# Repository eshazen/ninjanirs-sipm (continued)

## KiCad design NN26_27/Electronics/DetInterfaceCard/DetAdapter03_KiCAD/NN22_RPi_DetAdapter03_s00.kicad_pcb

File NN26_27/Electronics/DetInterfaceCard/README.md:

## Detector card V03

Two variants:

| Designator | NN24-26        | NN27  | Notes                             |
|------------|----------------|-------|-----------------------------------|
| R71        | DNP            | 0 Ohm | New component / designator        |
| LF1        | BLM18AG601SN1D | DNP   | Ferrite 600 Ohm @ 100 MHz, 500 mA |

Additional components could be DNP’d in NN27 if desired, such as U13 and C104.

**2026-08-24**

Trying to order.  Two problem parts:

C89 etc.  10uF X5R 0402

D1-D2  SBR1A20T5-7  1A fast response diode.  A problem.

Possible sub:  SBR1U40LP-7 in DFN package about the same size.
Make this change in `develop` (KiCAD conversion).  Layout done.

BOM is a problem... the KiCAD import doesnt include MPN.

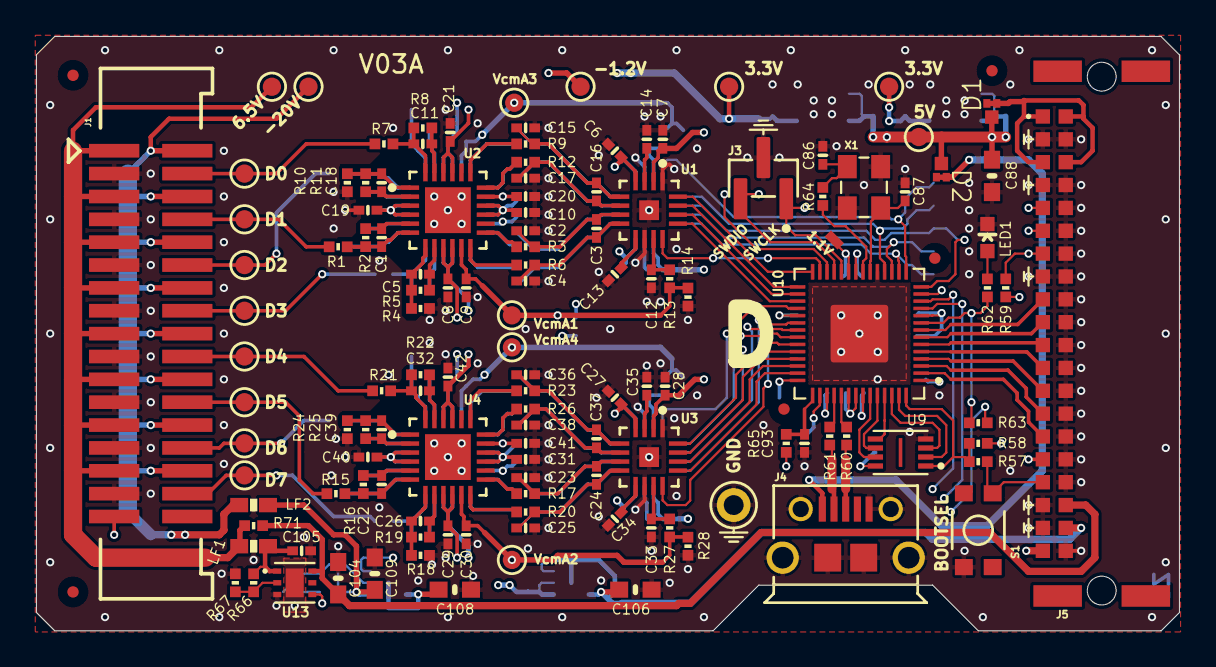
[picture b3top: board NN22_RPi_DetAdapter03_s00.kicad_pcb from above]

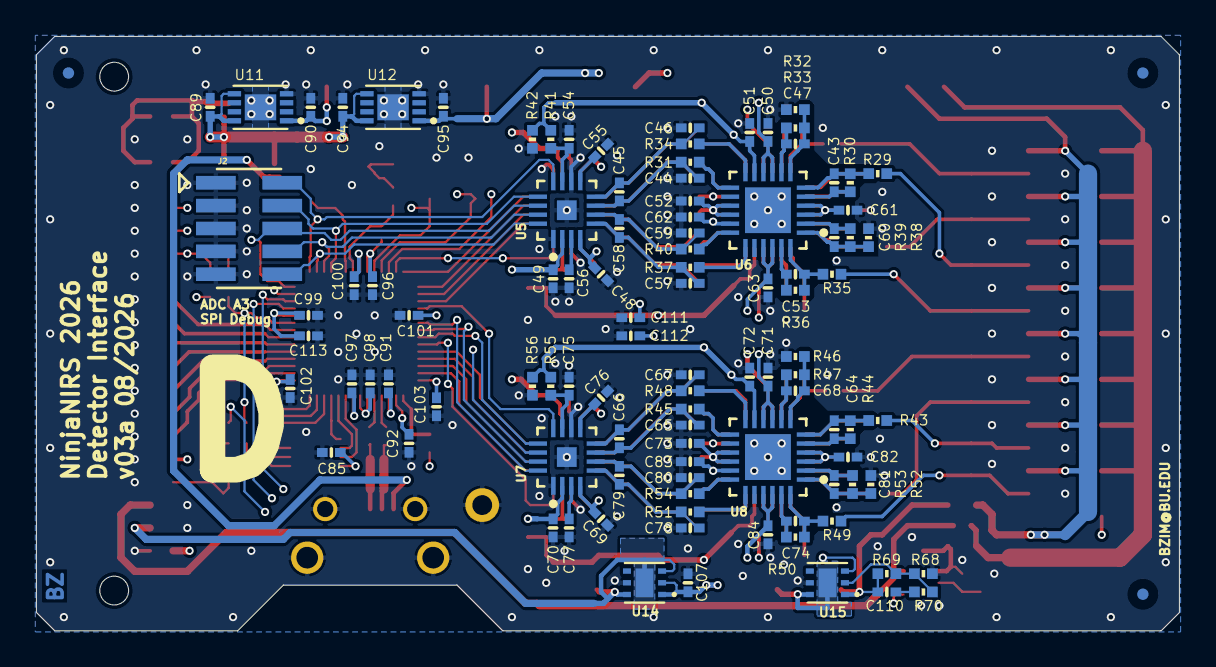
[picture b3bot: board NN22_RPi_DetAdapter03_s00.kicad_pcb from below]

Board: 6 copper layers, 63.5 x 33.0 mm, 239 parts (105 on the bottom side), 156 nets.

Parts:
C1, C5, C11, C18, C22, C26, C32, C39, C43, C47, C53, C60, C64, C68, C74, C81: 330p; 0402-CAP
C2, C3, C4, C15, C16, C17, C23, C24, C25, C36, C37, C38, C44, C45, C46, C57, C58, C59, C65, C66, C67, C78, C79, C80: 1n; 0402-CAP
C6, C7, C12, C14, C27, C28, C33, C35, C48, C49, C54, C56, C69, C70, C75, C77: 1u; 0402-CAP
C8, C9, C10, C13, C19, C20, C21, C29, C30, C31, C34, C40, C41, C42, C50, C51, C52, C55, C61, C62, C63, C71, C72, C73, C76, C82, C83, C84, C85, C96, C97, C98, C99, C100, C101, C102, C103: 0.1u; 0402-CAP
C86, C87: 27p; 0402-CAP
C88, C104, C106, C108, C109: 10u; 0603-CAP
C89, C90, C91, C92, C93, C94, C95, C105, C107, C111, C112, C113: 4.7u; 0402-CAP
C110: 33n; 0402-CAP
D1, D2: SBR1U40LP; DFN1411
FID1, FID2, FID3, FID4, FID5, FID6, FID7, FID8: FIDUCIALUFIDUCIAL; MICRO-FIDUCIAL
J1: M17X2; M17X2_0.050_SHF
J2: M05X2_SMD_0.050_NOCREAM; M05X2_0.050_SMD_NO_CREAM
J3: M03X1_0.050_SMD_NO_CREAM
J4: USB-MICRO
J5: M20X2_HARFLEX_M
LED1: LED0603; LED-0603
LF1, LF2: FERRITE0603; 0603-FER
R1, R4, R7, R10, R13, R14, R15, R18, R21, R24, R27, R28, R29, R32, R35, R38, R41, R42, R43, R46, R49, R52, R55, R56: 18k; 0402-RES
R2, R5, R8, R11, R16, R19, R22, R25, R30, R33, R36, R39, R44, R47, R50, R53: 2.2k; 0402-RES
R3, R6, R9, R12, R17, R20, R23, R26, R31, R34, R37, R40, R45, R48, R51, R54, R65: 33; 0402-RES
R57, R62, R64: 1.2k; 0402-RES
R58, R59, R67: 100k; 0402-RES
R60, R61: 27; 0402-RES
R63, R71: DNP; 0402-RES
R66: 30k; 0402-RES
R68, R70: 10k; 0402-RES
R69: 154k; 0402-RES
S1: SWITCH-MOMENTARY-2SMD-3; TACTILE_SWITCH_SMD-3
TP1, TP2, TP3, TP4, TP5, TP6, TP7, TP8, TP9, TP11, TP12, TP13, TP15, TP16, TP17, TP18, TP19, TP22: TESTPOINT_ROUND; TESTPAD_ROUND
TP20: TESTPOINT1X01; 1X01
TP21: TESTPOINTPADSMALL; TESTPAD_SMALL
U1, U3, U5, U7: AD7380; LFCSP16
U2, U4, U6, U8: ADA4940-2; LFCSP24
U9: W25Q_USON_PAD; USON8L-2X3MM_APM
U10: RP2040; QFN-56_EP
U11, U12: MCP1755_DFN; DFN8_2X3MM
U13: ADP7142_WSON; WSON6
U14, U15: ADP7182_WSON; WSON6
X1: CRYSTAL-3.2-2.5

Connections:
A_COMM: J1.33, R63.2
BOOTSEL: J5.B17 (33), R57.1, S1.4 (2)
DET0: J1.4, R7.1, TP4.P$1 (P$1_P$1)
DET1: J1.8, R1.1, TP1.P$1 (P$1_P$1)
DET2: J1.12, R29.1, TP9.P$1 (P$1_P$1)
DET3: J1.16, R35.1, TP11.P$1 (P$1_P$1)
DET4: J1.20, R21.1, TP7.P$1 (P$1_P$1)
DET5: J1.24, R15.1, TP6.P$1 (P$1_P$1)
DET6: J1.28, R43.1, TP13.P$1 (P$1_P$1)
DET7: J1.32, R49.1, TP15.P$1 (P$1_P$1)
GND: C2.1, C4.2, C6.2, C7.2, C8.2, C9.2, C10.2, C12.2, C13.2, C14.2, C15.1, C17.2, C19.2, C20.2, C21.2, C23.1, C25.2, C27.2, C28.2, C29.2, C30.2, C31.2, C33.2, C34.2, C35.2, C36.1, C38.2, C40.2, C41.2, C42.2, C44.1, C46.2, C48.2, C49.2, C50.2, C51.2, C52.2, C54.2, C55.2, C56.2, C57.1, C59.2, C61.2, C62.2, C63.2, C65.1, C67.2, C69.2, C70.2, C71.2, C72.2, C73.2, C75.2, C76.2, C77.2, C78.1, C80.2, C82.2, C83.2, C84.2, C85.2, C86.2, C87.2, C88.2, C89.2, C90.2, C91.2, C92.2, C93.2, C94.2, C95.2, C96.2, C97.2, C98.2, C99.2, C100.2, C101.2, C102.2, C103.2, C104.2, C105.2, C106.1, C107.1, C108.1, C109.1, C111.2, C112.1, C113.2, J1.3, J1.7, J1.11, J1.15, J1.19, J1.23, J1.27, J1.31, J2.1, J2.3, J2.5, J2.7, J2.9, J3.2, J4.5, J4.SH1, J4.SH2, J4.SH3, J4.SH4, J4.SH5, J4.SH6, J5.A2 (4), J5.A4 (8), J5.A5 (10), J5.A6 (12), J5.A7 (14), J5.A8 (16), J5.A9 (18), J5.A10 (20), J5.A11 (22), J5.A12 (24), J5.A13 (26), J5.A14 (28), J5.A15 (30), J5.A16 (32), J5.A17 (34), J5.A20 (40), J5.B2 (3), J5.B4 (7), J5.B8 (15), J5.B18 (35), J5.B19 (37), LED1.C, R4.1, R10.1, R14.1, R18.1, R24.1, R28.1, R32.1, R38.1, R42.1, R46.1, R52.1, R56.1, R67.1, R68.2, S1.1, TP20.1 (P$1_1), U1.1 (GND), U1.10 (GND), U1.EP (GND), U2.EP (1), U3.1 (GND), U3.10 (GND), U3.EP (GND), U4.EP (1), U5.1 (GND), U5.10 (GND), U5.EP (GND), U6.EP (1), U7.1 (GND), U7.10 (GND), U7.EP (GND), U8.EP (1), U9.4 (GND), U10.19 (TESTEN), U10.PAD (GND), U11.4 (GND), U11.P (GND), U12.4 (GND), U12.P (GND), U13.3 (GND), U13.PAD (GND), U14.5 (GND), U15.5 (GND), X1.2 (GND), X1.4 (GND)
GPIO00: J5.B15 (29), U10.2 (GPIO00)
GPIO01: J5.B14 (27), U10.3 (GPIO01)
GPIO02: J5.B13 (25), U10.4 (GPIO02)
GPIO03: J5.B12 (23), U10.5 (GPIO03)
GPIO04: J5.B11 (21), U10.6 (GPIO04)
GPIO05: J5.B10 (19), U10.7 (GPIO05)
GPIO06: J5.B9 (17), U10.8 (GPIO06)
LED: R62.2, R63.1, U10.9 (GPIO07)
unnamed: C110.1, R70.1
unnamed: J4.2, R61.2
unnamed: J4.3, R60.2
unnamed: LED1.A, R62.1
unnamed: J1.1, J1.5, J1.9, J1.13, J1.17, J1.21, J1.25, J1.29, LF1.1, R71.1, TP2.P$1 (P$1_P$1)
unnamed: J1.2, J1.6, J1.10, J1.14, J1.18, J1.22, J1.26, J1.30, LF2.1, TP3.P$1 (P$1_P$1)
unnamed: C3.2, C4.1, R6.2, U1.8 (AINA+)
unnamed: C2.2, C3.1, R3.2, U1.7 (AINA-)
unnamed: C16.2, C17.1, R12.2, U1.6 (AINB+)
unnamed: C15.2, C16.1, R9.2, U1.5 (AINB-)
unnamed: C13.1, U1.9 (REFCAP)
unnamed: C12.1, R13.2, U1.11 (REFIO)
unnamed: C14.1, U1.3 (REGCAP)
unnamed: C18.2, R11.2, U2.2 (+FB)
unnamed: C11.1, R7.2, R8.1, U2.24 (+IN)
unnamed: R12.1, U2.18 (+OUT)
unnamed: C11.2, R8.2, U2.23 (-FB)
unnamed: C18.1, R10.2, R11.1, U2.1 (-IN)
unnamed: R9.1, U2.19 (-OUT)
unnamed: C5.2, R5.2, U2.8 (+FB)
unnamed: C1.1, R1.2, R2.1, U2.6 (+IN)
unnamed: R6.1, U2.12 (+OUT)
unnamed: C1.2, R2.2, U2.5 (-FB)
unnamed: C5.1, R4.2, R5.1, U2.7 (-IN)
unnamed: R3.1, U2.13 (-OUT)
unnamed: C24.2, C25.1, R20.2, U3.8 (AINA+)
unnamed: C23.2, C24.1, R17.2, U3.7 (AINA-)
unnamed: C37.2, C38.1, R26.2, U3.6 (AINB+)
unnamed: C36.2, C37.1, R23.2, U3.5 (AINB-)
unnamed: C34.1, U3.9 (REFCAP)
unnamed: C33.1, R27.2, U3.11 (REFIO)
unnamed: C35.1, U3.3 (REGCAP)
unnamed: C39.2, R25.2, U4.2 (+FB)
unnamed: C32.1, R21.2, R22.1, U4.24 (+IN)
unnamed: R26.1, U4.18 (+OUT)
unnamed: C32.2, R22.2, U4.23 (-FB)
unnamed: C39.1, R24.2, R25.1, U4.1 (-IN)
unnamed: R23.1, U4.19 (-OUT)
unnamed: C26.2, R19.2, U4.8 (+FB)
unnamed: C22.1, R15.2, R16.1, U4.6 (+IN)
unnamed: R20.1, U4.12 (+OUT)
unnamed: C22.2, R16.2, U4.5 (-FB)
unnamed: C26.1, R18.2, R19.1, U4.7 (-IN)
unnamed: R17.1, U4.13 (-OUT)
unnamed: C45.2, C46.1, R34.2, U5.8 (AINA+)
unnamed: C44.2, C45.1, R31.2, U5.7 (AINA-)
unnamed: C58.2, C59.1, R40.2, U5.6 (AINB+)
unnamed: C57.2, C58.1, R37.2, U5.5 (AINB-)
unnamed: C55.1, U5.9 (REFCAP)
unnamed: C54.1, R41.2, U5.11 (REFIO)
unnamed: C56.1, U5.3 (REGCAP)
unnamed: C60.2, R39.2, U6.2 (+FB)
unnamed: C53.1, R35.2, R36.1, U6.24 (+IN)
unnamed: R40.1, U6.18 (+OUT)
unnamed: C53.2, R36.2, U6.23 (-FB)
unnamed: C60.1, R38.2, R39.1, U6.1 (-IN)
unnamed: R37.1, U6.19 (-OUT)
unnamed: C47.2, R33.2, U6.8 (+FB)
unnamed: C43.1, R29.2, R30.1, U6.6 (+IN)
unnamed: R34.1, U6.12 (+OUT)
unnamed: C43.2, R30.2, U6.5 (-FB)
unnamed: C47.1, R32.2, R33.1, U6.7 (-IN)
unnamed: R31.1, U6.13 (-OUT)
unnamed: C66.2, C67.1, R48.2, U7.8 (AINA+)
unnamed: C65.2, C66.1, R45.2, U7.7 (AINA-)
unnamed: C79.2, C80.1, R54.2, U7.6 (AINB+)
unnamed: C78.2, C79.1, R51.2, U7.5 (AINB-)
unnamed: C76.1, U7.9 (REFCAP)
unnamed: C75.1, R55.2, U7.11 (REFIO)
unnamed: C77.1, U7.3 (REGCAP)
unnamed: C81.2, R53.2, U8.2 (+FB)
unnamed: C74.1, R49.2, R50.1, U8.24 (+IN)
unnamed: R54.1, U8.18 (+OUT)
unnamed: C74.2, R50.2, U8.23 (-FB)
unnamed: C81.1, R52.2, R53.1, U8.1 (-IN)
unnamed: R51.1, U8.19 (-OUT)
unnamed: C68.2, R47.2, U8.8 (+FB)
unnamed: C64.1, R43.2, R44.1, U8.6 (+IN)
unnamed: R48.1, U8.12 (+OUT)
unnamed: C64.2, R44.2, U8.5 (-FB)
unnamed: C68.1, R46.2, R47.1, U8.7 (-IN)
unnamed: R45.1, U8.13 (-OUT)
unnamed: R61.1, U10.46 (USB_DN)
unnamed: R60.1, U10.47 (USB_DP)
unnamed: C87.1, U10.20 (XIN), X1.3 (C2)
unnamed: R64.1, U10.21 (XOUT)
unnamed: C93.1, R65.2, U10.43 (ADC_VDD)
unnamed: R66.1, R67.2, U13.2 (SENSE/ADJ)
unnamed: R68.1, R69.2, R70.2, U15.2 (NC/ADJ)
unnamed: C86.1, R64.2, X1.1 (C1)
OPT_EN_VN: U10.12 (GPIO09), U15.3 (EN)
OPT_EN_VP: U10.11 (GPIO08), U13.4 (EN)
QSPI_SCLK: U9.6 (CLK), U10.52 (QSPI_SCLK)
QSPI_SD0: U9.5 (DI/IO[0]), U10.53 (QSPI_SD0)
QSPI_SD1: U9.2 (DO/IO[1]), U10.55 (QSPI_SD1)
QSPI_SD2: U9.3 (#WP/IO[2]), U10.54 (QSPI_SD2)
QSPI_SD3: U9.7 (#HOLD/IO[3]), U10.51 (QSPI_SD3)
QSPI_SS_N: R57.2, R58.1, U9.1 (/CS), U10.56 (QSPI_SS_N)
RUN: J5.B7 (13), R59.1, U10.26 (RUN)
SCLK_A1: U1.16 (SCLK), U10.28 (GPIO17)
SCLK_A2: U3.16 (SCLK), U10.38 (GPIO26/ADC0)
SCLK_A3: J2.10, U5.16 (SCLK), U10.16 (GPIO13)
SCLK_A4: U7.16 (SCLK), U10.34 (GPIO22)
SDI_A1: U1.15 (SDI), U10.29 (GPIO18)
SDI_A2: U3.15 (SDI), U10.39 (GPIO27/ADC1)
SDI_A3: J2.8, U5.15 (SDI), U10.17 (GPIO14)
SDI_A4: U7.15 (SDI), U10.35 (GPIO23)
SDOA_A1: U1.13 (SDOA), U10.31 (GPIO20)
SDOA_A2: U3.13 (SDOA), U10.41 (GPIO29/ADC3)
SDOA_A3: J2.4, U5.13 (SDOA), U10.18 (GPIO15)
SDOA_A4: U7.13 (SDOA), U10.36 (GPIO24)
SDOB_A1: U1.14 (SDOB), U10.30 (GPIO19)
SDOB_A2: U3.14 (SDOB), U10.40 (GPIO28/ADC2)
SDOB_A3: J2.6, U5.14 (SDOB), U10.14 (GPIO11)
SDOB_A4: U7.14 (SDOB), U10.13 (GPIO10)
SWCLK: J3.1, J5.B6 (11), U10.24 (SWCLK)
SWDIO: J3.3, J5.B5 (9), U10.25 (SWDIO)
V1P1: C91.1, C96.1, C97.1, TP21.P$1 (P$1_P$1), U10.23 (DVDD), U10.45 (VREG_VOUT), U10.50 (DVDD)
V3P3: C7.1, C28.1, C49.1, C70.1, C85.1, C90.1, C92.1, C98.1, C99.1, C100.1, C101.1, C102.1, C103.1, C113.1, J5.B16 (31), R58.2, R59.2, R65.1, TP17.P$1 (P$1_P$1), U1.2 (VLOGIC), U3.2 (VLOGIC), U5.2 (VLOGIC), U7.2 (VLOGIC), U9.8 (VCC), U10.1 (IOVDD), U10.10 (IOVDD), U10.22 (IOVDD), U10.33 (IOVDD), U10.42 (IOVDD), U10.44 (VREG_VIN), U10.48 (USB_VDD), U10.49 (IOVDD), U11.1 (OUT)
V3P3A: C6.1, C8.1, C19.1, C27.1, C29.1, C40.1, C48.1, C50.1, C61.1, C69.1, C71.1, C82.1, C95.1, C111.1, TP18.P$1 (P$1_P$1), U1.4 (VCC), U2.3 (+VS), U2.4 (+VS), U2.9 (+VS), U2.10 (+VS), U3.4 (VCC), U4.3 (+VS), U4.4 (+VS), U4.9 (+VS), U4.10 (+VS), U5.4 (VCC), U6.3 (+VS), U6.4 (+VS), U6.9 (+VS), U6.10 (+VS), U7.4 (VCC), U8.3 (+VS), U8.4 (+VS), U8.9 (+VS), U8.10 (+VS), U12.1 (OUT)
V5P0: C88.1, C89.1, C94.1, D1.1 (K), D2.1 (K), TP22.P$1 (P$1_P$1), U11.5 (/SHDN), U11.8 (IN), U12.5 (/SHDN), U12.8 (IN)
V5P0_IN: D1.2 (A), D1.3 (A), J5.A1 (2), J5.A3 (6), J5.B1 (1), J5.B3 (5)
V6P5: C105.1, LF1.2, R66.2, U13.1 (VOUT)
V9P0: C104.1, J5.A18 (36), R71.2, U13.6 (VIN)
VBUS: D2.2 (A), D2.3 (A), J4.1
VN1P2: C10.1, C21.1, C31.1, C42.1, C52.1, C63.1, C73.1, C84.1, C107.2, C112.2, TP19.P$1 (P$1_P$1), U2.15 (-VS), U2.16 (-VS), U2.21 (-VS), U2.22 (-VS), U4.15 (-VS), U4.16 (-VS), U4.21 (-VS), U4.22 (-VS), U6.15 (-VS), U6.16 (-VS), U6.21 (-VS), U6.22 (-VS), U8.15 (-VS), U8.16 (-VS), U8.21 (-VS), U8.22 (-VS), U14.1 (OUT), U14.2 (NC/ADJ)
VN3P0: C106.2, J5.A19 (38), U14.3 (EN), U14.6 (IN), U14.PAD (IN)
VN20P0: C109.2, C110.2, LF2.2, R69.1, U15.1 (OUT)
VN22: C108.2, J5.B20 (39), U15.6 (IN), U15.PAD (IN)
VOCM_A1: C9.1, C20.1, R13.1, R14.2, TP5.P$1 (P$1_P$1), U2.11 (VOCM), U2.17 (VOCM)
VOCM_A2: C30.1, C41.1, R27.1, R28.2, TP8.P$1 (P$1_P$1), U4.11 (VOCM), U4.17 (VOCM)
VOCM_A3: C51.1, C62.1, R41.1, R42.2, TP12.P$1 (P$1_P$1), U6.11 (VOCM), U6.17 (VOCM)
VOCM_A4: C72.1, C83.1, R55.1, R56.2, TP16.P$1 (P$1_P$1), U8.11 (VOCM), U8.17 (VOCM)
/CS_A1: U1.12 (/CS), U10.27 (GPIO16)
/CS_A2: U3.12 (/CS), U10.37 (GPIO25)
/CS_A3: J2.2, U5.12 (/CS), U10.15 (GPIO12)
/CS_A4: U7.12 (/CS), U10.32 (GPIO21)

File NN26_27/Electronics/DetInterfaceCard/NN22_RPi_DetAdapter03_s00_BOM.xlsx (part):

Designator | Value | Footprint | Populate | MPN | Manufacturer
C1 | 330p | 0402-CAP | 1 | GRM1555C1H331JA01D | Murata
C10 | 0.1u | 0402-CAP | 1 | GRM155R71H104KE14D | Murata
C100 | 0.1u | 0402-CAP | 1 | GRM155R71H104KE14D | Murata
C101 | 0.1u | 0402-CAP | 1 | GRM155R71H104KE14D | Murata
C102 | 0.1u | 0402-CAP | 1 | GRM155R71H104KE14D | Murata
C103 | 0.1u | 0402-CAP | 1 | GRM155R71H104KE14D | Murata
C104 | 10u | 0603-CAP | 1 | GRM188R6YA106MA73D | Murata
C105 | 4.7u | 0402-CAP | 1 | CL05A475MP5NRNC | Samsung
C106 | 10u | 0603-CAP | 1 | GRM188R6YA106MA73D | Murata
C107 | 4.7u | 0402-CAP | 1 | CL05A475MP5NRNC | Samsung
C108 | 10u | 0603-CAP | 1 | GRM188R6YA106MA73D | Murata
C109 | 10u | 0603-CAP | 1 | GRM188R6YA106MA73D | Murata
C11 | 330p | 0402-CAP | 1 | GRM1555C1H331JA01D | Murata
C110 | 33n | 0402-CAP | 1 | GCM155R71E333KA55D | Murata
C111 | 4.7u | 0402-CAP | 1 | CL05A475MP5NRNC | Samsung
C112 | 4.7u | 0402-CAP | 1 | CL05A475MP5NRNC | Samsung
C113 | 4.7u | 0402-CAP | 1 | CL05A475MP5NRNC | Samsung
C12 | 1u | 0402-CAP | 1 | CL05A105KP5NNNC | Samsung
C13 | 0.1u | 0402-CAP | 1 | GRM155R71H104KE14D | Murata
C14 | 1u | 0402-CAP | 1 | CL05A105KP5NNNC | Samsung
C15 | 1n | 0402-CAP | 1 | GRM1555C1H102JA01D | Murata
C16 | 1n | 0402-CAP | 1 | GRM1555C1H102JA01D | Murata
C17 | 1n | 0402-CAP | 1 | GRM1555C1H102JA01D | Murata
C18 | 330p | 0402-CAP | 1 | GRM1555C1H331JA01D | Murata
C19 | 0.1u | 0402-CAP | 1 | GRM155R71H104KE14D | Murata
C2 | 1n | 0402-CAP | 1 | GRM1555C1H102JA01D | Murata
C20 | 0.1u | 0402-CAP | 1 | GRM155R71H104KE14D | Murata
C21 | 0.1u | 0402-CAP | 1 | GRM155R71H104KE14D | Murata
C22 | 330p | 0402-CAP | 1 | GRM1555C1H331JA01D | Murata
C23 | 1n | 0402-CAP | 1 | GRM1555C1H102JA01D | Murata
C24 | 1n | 0402-CAP | 1 | GRM1555C1H102JA01D | Murata
C25 | 1n | 0402-CAP | 1 | GRM1555C1H102JA01D | Murata
C26 | 330p | 0402-CAP | 1 | GRM1555C1H331JA01D | Murata
C27 | 1u | 0402-CAP | 1 | CL05A105KP5NNNC | Samsung
C28 | 1u | 0402-CAP | 1 | CL05A105KP5NNNC | Samsung
C29 | 0.1u | 0402-CAP | 1 | GRM155R71H104KE14D | Murata
C3 | 1n | 0402-CAP | 1 | GRM1555C1H102JA01D | Murata
C30 | 0.1u | 0402-CAP | 1 | GRM155R71H104KE14D | Murata
C31 | 0.1u | 0402-CAP | 1 | GRM155R71H104KE14D | Murata
C32 | 330p | 0402-CAP | 1 | GRM1555C1H331JA01D | Murata
C33 | 1u | 0402-CAP | 1 | CL05A105KP5NNNC | Samsung
C34 | 0.1u | 0402-CAP | 1 | GRM155R71H104KE14D | Murata
C35 | 1u | 0402-CAP | 1 | CL05A105KP5NNNC | Samsung
C36 | 1n | 0402-CAP | 1 | GRM1555C1H102JA01D | Murata
C37 | 1n | 0402-CAP | 1 | GRM1555C1H102JA01D | Murata
C38 | 1n | 0402-CAP | 1 | GRM1555C1H102JA01D | Murata
C39 | 330p | 0402-CAP | 1 | GRM1555C1H331JA01D | Murata
C4 | 1n | 0402-CAP | 1 | GRM1555C1H102JA01D | Murata
C40 | 0.1u | 0402-CAP | 1 | GRM155R71H104KE14D | Murata
C41 | 0.1u | 0402-CAP | 1 | GRM155R71H104KE14D | Murata
C42 | 0.1u | 0402-CAP | 1 | GRM155R71H104KE14D | Murata
C43 | 330p | 0402-CAP | 1 | GRM1555C1H331JA01D | Murata
C44 | 1n | 0402-CAP | 1 | GRM1555C1H102JA01D | Murata
C45 | 1n | 0402-CAP | 1 | GRM1555C1H102JA01D | Murata
C46 | 1n | 0402-CAP | 1 | GRM1555C1H102JA01D | Murata
C47 | 330p | 0402-CAP | 1 | GRM1555C1H331JA01D | Murata
C48 | 1u | 0402-CAP | 1 | CL05A105KP5NNNC | Samsung
C49 | 1u | 0402-CAP | 1 | CL05A105KP5NNNC | Samsung
C5 | 330p | 0402-CAP | 1 | GRM1555C1H331JA01D | Murata
C50 | 0.1u | 0402-CAP | 1 | GRM155R71H104KE14D | Murata
C51 | 0.1u | 0402-CAP | 1 | GRM155R71H104KE14D | Murata
C52 | 0.1u | 0402-CAP | 1 | GRM155R71H104KE14D | Murata
C53 | 330p | 0402-CAP | 1 | GRM1555C1H331JA01D | Murata
C54 | 1u | 0402-CAP | 1 | CL05A105KP5NNNC | Samsung
C55 | 0.1u | 0402-CAP | 1 | GRM155R71H104KE14D | Murata
C56 | 1u | 0402-CAP | 1 | CL05A105KP5NNNC | Samsung
C57 | 1n | 0402-CAP | 1 | GRM1555C1H102JA01D | Murata
C58 | 1n | 0402-CAP | 1 | GRM1555C1H102JA01D | Murata
C59 | 1n | 0402-CAP | 1 | GRM1555C1H102JA01D | Murata
C6 | 1u | 0402-CAP | 1 | CL05A105KP5NNNC | Samsung
C60 | 330p | 0402-CAP | 1 | GRM1555C1H331JA01D | Murata
C61 | 0.1u | 0402-CAP | 1 | GRM155R71H104KE14D | Murata
C62 | 0.1u | 0402-CAP | 1 | GRM155R71H104KE14D | Murata
C63 | 0.1u | 0402-CAP | 1 | GRM155R71H104KE14D | Murata
C64 | 330p | 0402-CAP | 1 | GRM1555C1H331JA01D | Murata
C65 | 1n | 0402-CAP | 1 | GRM1555C1H102JA01D | Murata
C66 | 1n | 0402-CAP | 1 | GRM1555C1H102JA01D | Murata
C67 | 1n | 0402-CAP | 1 | GRM1555C1H102JA01D | Murata
C68 | 330p | 0402-CAP | 1 | GRM1555C1H331JA01D | Murata
C69 | 1u | 0402-CAP | 1 | CL05A105KP5NNNC | Samsung
C7 | 1u | 0402-CAP | 1 | CL05A105KP5NNNC | Samsung
C70 | 1u | 0402-CAP | 1 | CL05A105KP5NNNC | Samsung
C71 | 0.1u | 0402-CAP | 1 | GRM155R71H104KE14D | Murata
C72 | 0.1u | 0402-CAP | 1 | GRM155R71H104KE14D | Murata
C73 | 0.1u | 0402-CAP | 1 | GRM155R71H104KE14D | Murata
C74 | 330p | 0402-CAP | 1 | GRM1555C1H331JA01D | Murata
C75 | 1u | 0402-CAP | 1 | CL05A105KP5NNNC | Samsung
C76 | 0.1u | 0402-CAP | 1 | GRM155R71H104KE14D | Murata
C77 | 1u | 0402-CAP | 1 | CL05A105KP5NNNC | Samsung
C78 | 1n | 0402-CAP | 1 | GRM1555C1H102JA01D | Murata
C79 | 1n | 0402-CAP | 1 | GRM1555C1H102JA01D | Murata
C8 | 0.1u | 0402-CAP | 1 | GRM155R71H104KE14D | Murata
C80 | 1n | 0402-CAP | 1 | GRM1555C1H102JA01D | Murata
C81 | 330p | 0402-CAP | 1 | GRM1555C1H331JA01D | Murata
C82 | 0.1u | 0402-CAP | 1 | GRM155R71H104KE14D | Murata
C83 | 0.1u | 0402-CAP | 1 | GRM155R71H104KE14D | Murata
C84 | 0.1u | 0402-CAP | 1 | GRM155R71H104KE14D | Murata
C85 | 0.1u | 0402-CAP | 1 | GRM155R71H104KE14D | Murata
C86 | 27p | 0402-CAP | 1 | GCM1555C1H270JA16D | Murata
C87 | 27p | 0402-CAP | 1 | GCM1555C1H270JA16D | Murata
C88 | 10u | 0603-CAP | 1 | GRM188R6YA106MA73D | Murata
C89 | 4.7u | 0402-CAP | 1 | CL05A475MP5NRNC | Samsung
C9 | 0.1u | 0402-CAP | 1 | GRM155R71H104KE14D | Murata
C90 | 4.7u | 0402-CAP | 1 | CL05A475MP5NRNC | Samsung
C91 | 4.7u | 0402-CAP | 1 | CL05A475MP5NRNC | Samsung
C92 | 4.7u | 0402-CAP | 1 | CL05A475MP5NRNC | Samsung
C93 | 4.7u | 0402-CAP | 1 | CL05A475MP5NRNC | Samsung
C94 | 4.7u | 0402-CAP | 1 | CL05A475MP5NRNC | Samsung
C95 | 4.7u | 0402-CAP | 1 | CL05A475MP5NRNC | Samsung
C96 | 0.1u | 0402-CAP | 1 | GRM155R71H104KE14D | Murata
C97 | 0.1u | 0402-CAP | 1 | GRM155R71H104KE14D | Murata
C98 | 0.1u | 0402-CAP | 1 | GRM155R71H104KE14D | Murata
C99 | 0.1u | 0402-CAP | 1 | GRM155R71H104KE14D | Murata
D1 | SBR1A20T5 | SOD523 | 1 | SBR1A20T5-7 | Diodes Inc.
D2 | SBR1A20T5 | SOD523 | 1 | SBR1A20T5-7 | Diodes Inc.
FID1 | FIDUCIALUFIDUCIAL | MICRO-FIDUCIAL | 0
FID2 | FIDUCIALUFIDUCIAL | MICRO-FIDUCIAL | 0
FID3 | FIDUCIALUFIDUCIAL | MICRO-FIDUCIAL | 0
FID4 | FIDUCIALUFIDUCIAL | MICRO-FIDUCIAL | 0
FID5 | FIDUCIALUFIDUCIAL | MICRO-FIDUCIAL | 0
FID6 | FIDUCIALUFIDUCIAL | MICRO-FIDUCIAL | 0
FID7 | FIDUCIALUFIDUCIAL | MICRO-FIDUCIAL | 0
FID8 | FIDUCIALUFIDUCIAL | MICRO-FIDUCIAL | 0
J1 | M17X2 | M17X2_0.050_SHF | 1 | SHF-117-01-L-D-SM | Samtec
J2 | M05X2_SMD_0.050_NOCREAM | M05X2_0.050_SMD_NO_CREAM | 0
J3 | M03X1_0.050_SMD_NO_CREAM | M03X1_0.050_SMD_NO_CREAM | 0
J4 | USB-MICRO | USB-MICRO | 1 | 10118194-0001LF | Amphenol Communications Solutions
J5 | M20X2_HARFLEX_M | M20X2_HARFLEX_M | 1 | 15150402601000 | HARTING Elektronik
LED1 |  | LED-0603 | 1 | LTST-C191KRKT | Lite-On
LF1 | FERRITE0603 | 0603-FER | 1 | BLM18AG601SN1D | Murata
LF2 | FERRITE0603 | 0603-FER | 1 | BLM18AG601SN1D | Murata
R1 | 18k | 0402-RES | 1 | RR0510P-183-D | Susumu
R10 | 18k | 0402-RES | 1 | RR0510P-183-D | Susumu
R11 | 2.2k | 0402-RES | 1 | RR0510P-222-D | Susumu
R12 | 33 | 0402-RES | 1 | CRCW040233R0FKEDC | Vishay
R13 | 18k | 0402-RES | 1 | RR0510P-183-D | Susumu
R14 | 18k | 0402-RES | 1 | RR0510P-183-D | Susumu
R15 | 18k | 0402-RES | 1 | RR0510P-183-D | Susumu
R16 | 2.2k | 0402-RES | 1 | RR0510P-222-D | Susumu
R17 | 33 | 0402-RES | 1 | CRCW040233R0FKEDC | Vishay
R18 | 18k | 0402-RES | 1 | RR0510P-183-D | Susumu
R19 | 2.2k | 0402-RES | 1 | RR0510P-222-D | Susumu
R2 | 2.2k | 0402-RES | 1 | RR0510P-222-D | Susumu
R20 | 33 | 0402-RES | 1 | CRCW040233R0FKEDC | Vishay
R21 | 18k | 0402-RES | 1 | RR0510P-183-D | Susumu
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
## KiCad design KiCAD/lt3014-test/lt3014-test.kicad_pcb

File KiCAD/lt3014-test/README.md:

# SiPM power regulator test board

This is a test board to provide the following features.  It is
intended to take as input ~65V bulk power from BZ's boost converter.

The final version would be stripped down to minimal parts and small
package sizes to fit on a future version of the detector adapter board.

* LT3014 high voltage regulator, programmable from 32-62V using a digital pot
* INA121 current sense / trip circuit.  Nominally set to trip at 10mA current but easy to change via resistor swap. 
* Set up (hopefully) to power up in a tripped state (HV off) until the R-Pi turns on the power
* Ability to measure output voltage and load current via R-Pi
* Socket for a Raspberry Pi Pico board for testing the interfaces.
* Testpoints and LEDs

## Revision History

* V1.0 - never fabricated
* V1.0a - as built with small changes suggested by BZ

## Debug log

### 2025-05-27
* Install Thonny on PC and micropython on the R-Pi.  Blinky working.
* Writing to the digital pot seems to work, but can't read back for some reason.

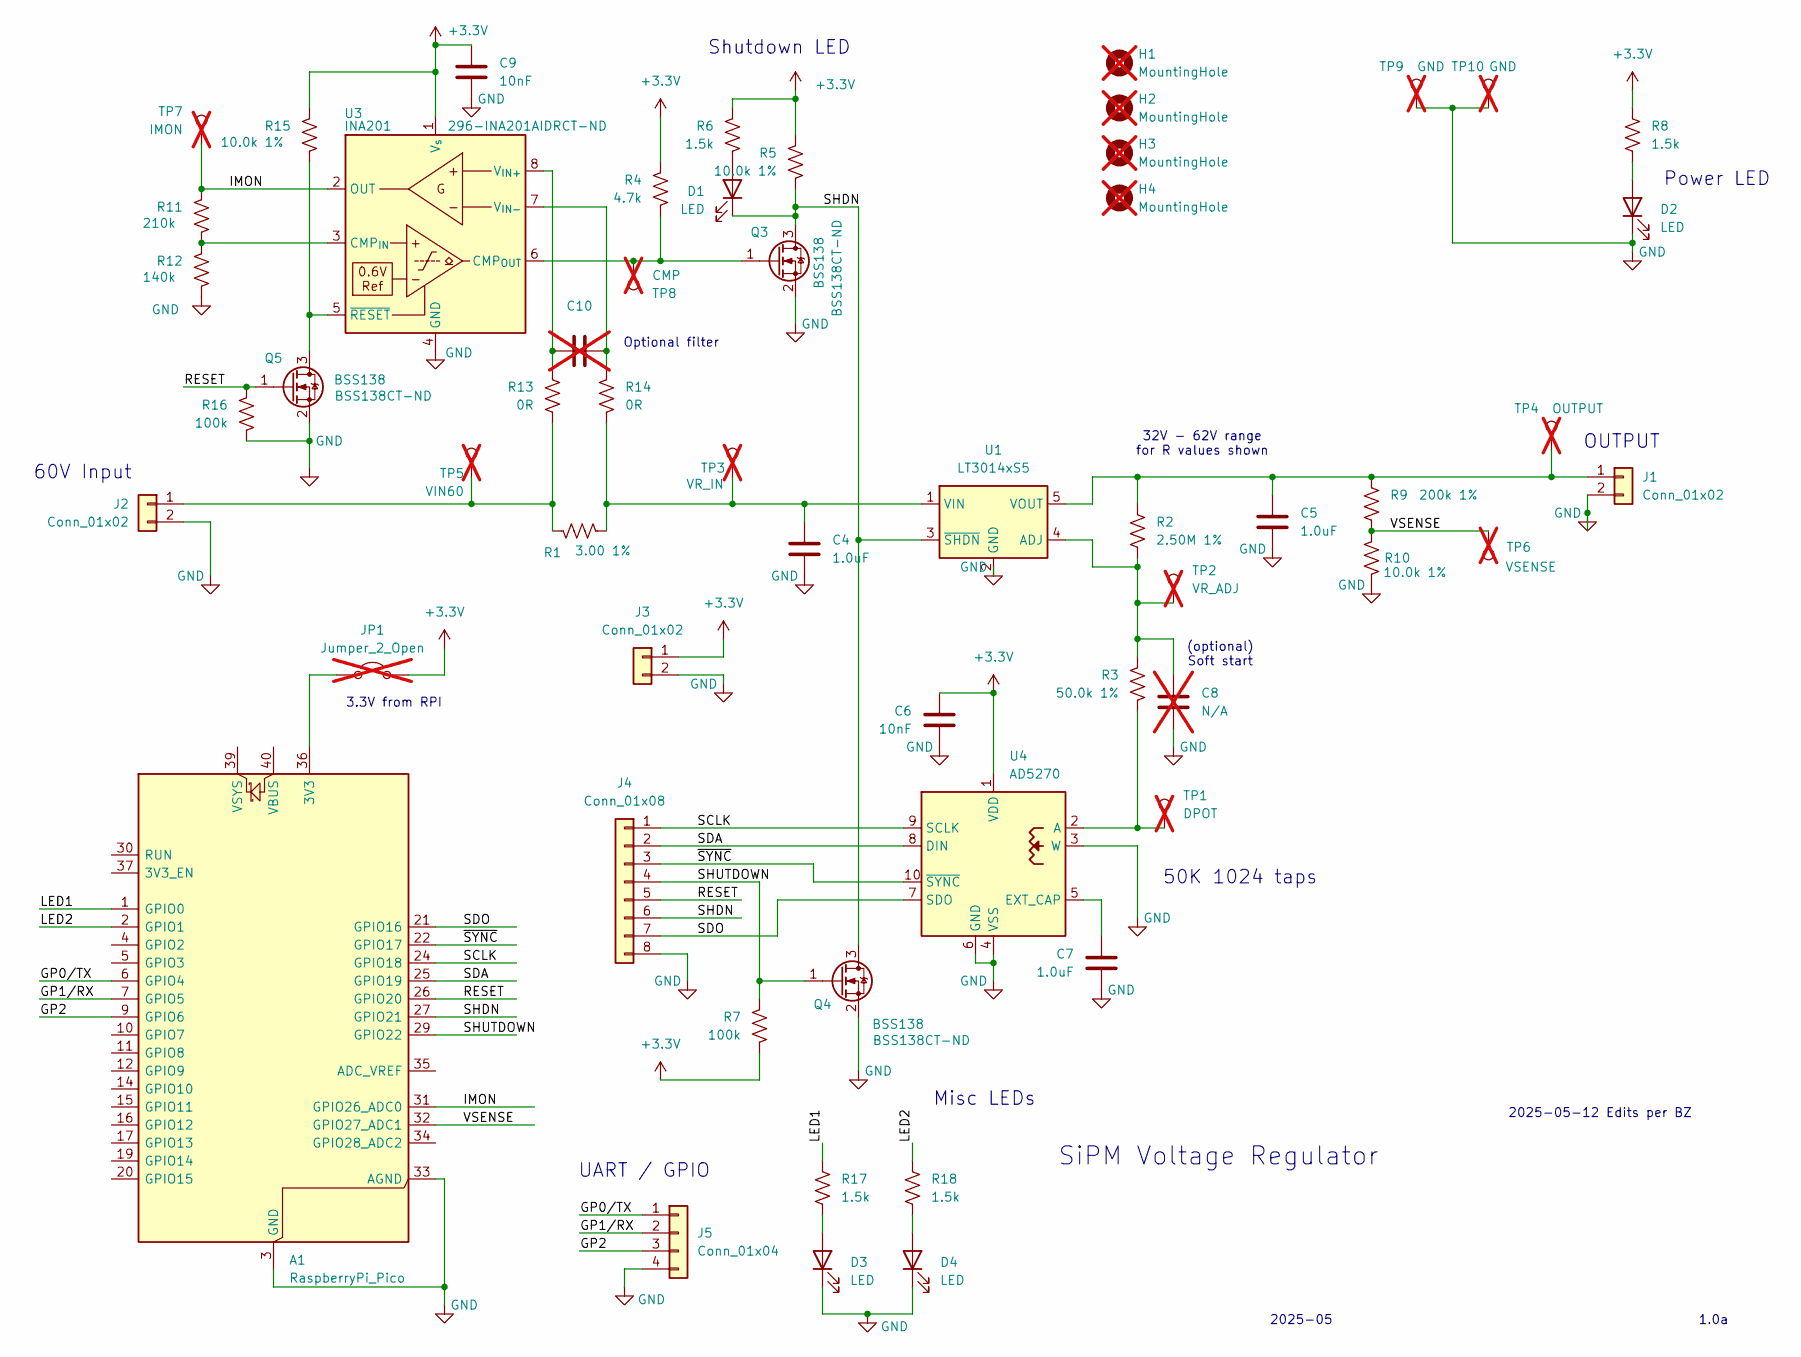
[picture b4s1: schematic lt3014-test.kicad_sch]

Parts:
A1: RaspberryPi_Pico; RaspberryPi_Pico_Common_Unspecified
C4, C5, C7: 1.0uF; C_0603_1608Metric_Pad1.08x0.95mm_HandSolder
C6, C9: 10nF; C_0603_1608Metric_Pad1.08x0.95mm_HandSolder
C8: N/A; C_0603_1608Metric_Pad1.08x0.95mm_HandSolder; not fitted
C10: C_0603_1608Metric_Pad1.08x0.95mm_HandSolder; not fitted
D1, D2, D3, D4: LED; my_SMT_0603
H1, H2, H3, H4: MountingHole; MountingHole_4.3mm_M4; not fitted
J1, J2, J3: Conn_01x02; PinHeader_1x02_P2.54mm_Vertical
J4: Conn_01x08; PinHeader_1x08_P2.54mm_Vertical
J5: Conn_01x04; PinHeader_1x04_P2.54mm_Vertical
JP1: Jumper_2_Open; PinHeader_1x02_P2.54mm_Vertical; not fitted
Q3, Q4, Q5: BSS138; SOT-23
R1: 3.00 1%; R_0603_1608Metric_Pad0.98x0.95mm_HandSolder
R2: 2.50M 1%; R_0603_1608Metric_Pad0.98x0.95mm_HandSolder
R3: 50.0k 1%; R_0603_1608Metric_Pad0.98x0.95mm_HandSolder
R4: 4.7k; R_0603_1608Metric_Pad0.98x0.95mm_HandSolder
R5, R10, R15: 10.0k 1%; R_0603_1608Metric_Pad0.98x0.95mm_HandSolder
R6, R8, R17, R18: 1.5k; R_0603_1608Metric_Pad0.98x0.95mm_HandSolder
R7, R16: 100k; R_0603_1608Metric_Pad0.98x0.95mm_HandSolder
R9: 200k 1%; R_0603_1608Metric_Pad0.98x0.95mm_HandSolder
R11: 210k; R_0603_1608Metric_Pad0.98x0.95mm_HandSolder
R12: 140k; R_0603_1608Metric_Pad0.98x0.95mm_HandSolder
R13, R14: 0R; R_0603_1608Metric_Pad0.98x0.95mm_HandSolder
TP1: DPOT; tp_SMT_label2; not fitted
TP2: VR_ADJ; tp_SMT_label2; not fitted
TP3: VR_IN; tp_SMT_label2; not fitted
TP4: OUTPUT; tp_SMT_label2; not fitted
TP5: VIN60; tp_SMT_label2; not fitted
TP6: VSENSE; tp_SMT_label2; not fitted
TP7: IMON; tp_SMT_label2; not fitted
TP8: CMP; tp_SMT_label2; not fitted
TP9, TP10: GND; tp_SMT_label2; not fitted
U1: LT3014xS5; SOT-23-5
U3: INA201; SOIC-8_3.9x4.9mm_P1.27mm
U4: AD5270; MSOP-10_3x3mm_P0.5mm

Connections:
+3.3V: C6.1, C9.1, J3.1, JP1.2 (B), R4.1, R5.1, R6.1, R7.2, R8.1, R15.1, U3.1 (V_{s}), U4.1 (VDD)
/GP0/TX: A1.6 (GPIO4), J5.1
/GP1/RX: A1.7 (GPIO5), J5.2
/GP2: A1.9 (GPIO6), J5.3
/IMON: A1.31 (GPIO26_ADC0), R11.1, TP7.1, U3.2 (OUT)
/LED1: A1.1 (GPIO0), R17.1
/LED2: A1.2 (GPIO1), R18.1
/RESET: A1.26 (GPIO20), J4.5, Q5.1 (G), R16.1
/SCLK: A1.24 (GPIO18), J4.1, U4.9 (SCLK)
/SDA: A1.25 (GPIO19), J4.2, U4.8 (DIN)
/SDO: A1.21 (GPIO16), J4.7, U4.7 (SDO)
/SHDN: A1.27 (GPIO21), D1.1 (K), J4.6, Q3.3 (D), Q4.3 (D), R5.2, U1.3 (~SHDN)
/SHUTDOWN: A1.29 (GPIO22), J4.4, Q4.1 (G), R7.1
/VSENSE: A1.32 (GPIO27_ADC1), R9.2, R10.1, TP6.1
/~SYNC: A1.22 (GPIO17), J4.3, U4.10 (~SYNC)
GND: A1.3 (GND), A1.8 (GND), A1.13 (GND), A1.18 (GND), A1.23 (GND), A1.28 (GND), A1.33 (AGND), A1.38 (GND), C4.2, C5.2, C6.2, C7.2, C8.2, C9.2, D2.1 (K), D3.1 (K), D4.1 (K), J1.2, J2.2, J3.2, J4.8, J5.4, Q3.2 (S), Q4.2 (S), Q5.2 (S), R10.2, R12.2, R16.2, TP9.1, TP10.1, U1.2 (GND), U3.4 (GND), U4.3 (W), U4.4 (VSS), U4.6 (GND)
unnamed: A1.36 (3V3), JP1.1 (A)
unnamed: D1.2 (A), R6.2
unnamed: D2.2 (A), R8.2
unnamed: D3.2 (A), R17.2
unnamed: D4.2 (A), R18.2
unnamed: C5.1, J1.1, R2.1, R9.1, TP4.1, U1.5 (VOUT)
unnamed: J2.1, R1.1, R13.2, TP5.1
unnamed: Q3.1 (G), R4.2, TP8.1, U3.6 (CMP_{OUT})
unnamed: Q5.3 (D), R15.2, U3.5 (~RESET)
unnamed: C8.1, R2.2, R3.1, TP2.1, U1.4 (ADJ)
unnamed: C4.1, R1.2, R14.2, TP3.1, U1.1 (VIN)
unnamed: R11.2, R12.1, U3.3 (CMP_{IN})
unnamed: C10.1, R13.1, U3.8 (V_{IN+})
unnamed: C10.2, R14.1, U3.7 (V_{IN-})
unnamed: R3.2, TP1.1, U4.2 (A)
unnamed: C7.1, U4.5 (EXT_CAP)

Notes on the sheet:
Misc LEDs
2025-05-12 Edits per BZ
OUTPUT
Shutdown LED
(optional) Soft start
2025-05
1.0a
Power LED
60V Input
3.3V from RPI
SiPM Voltage Regulator
32V - 62V range for R values shown
Optional filter
UART / GPIO
50K 1024 taps

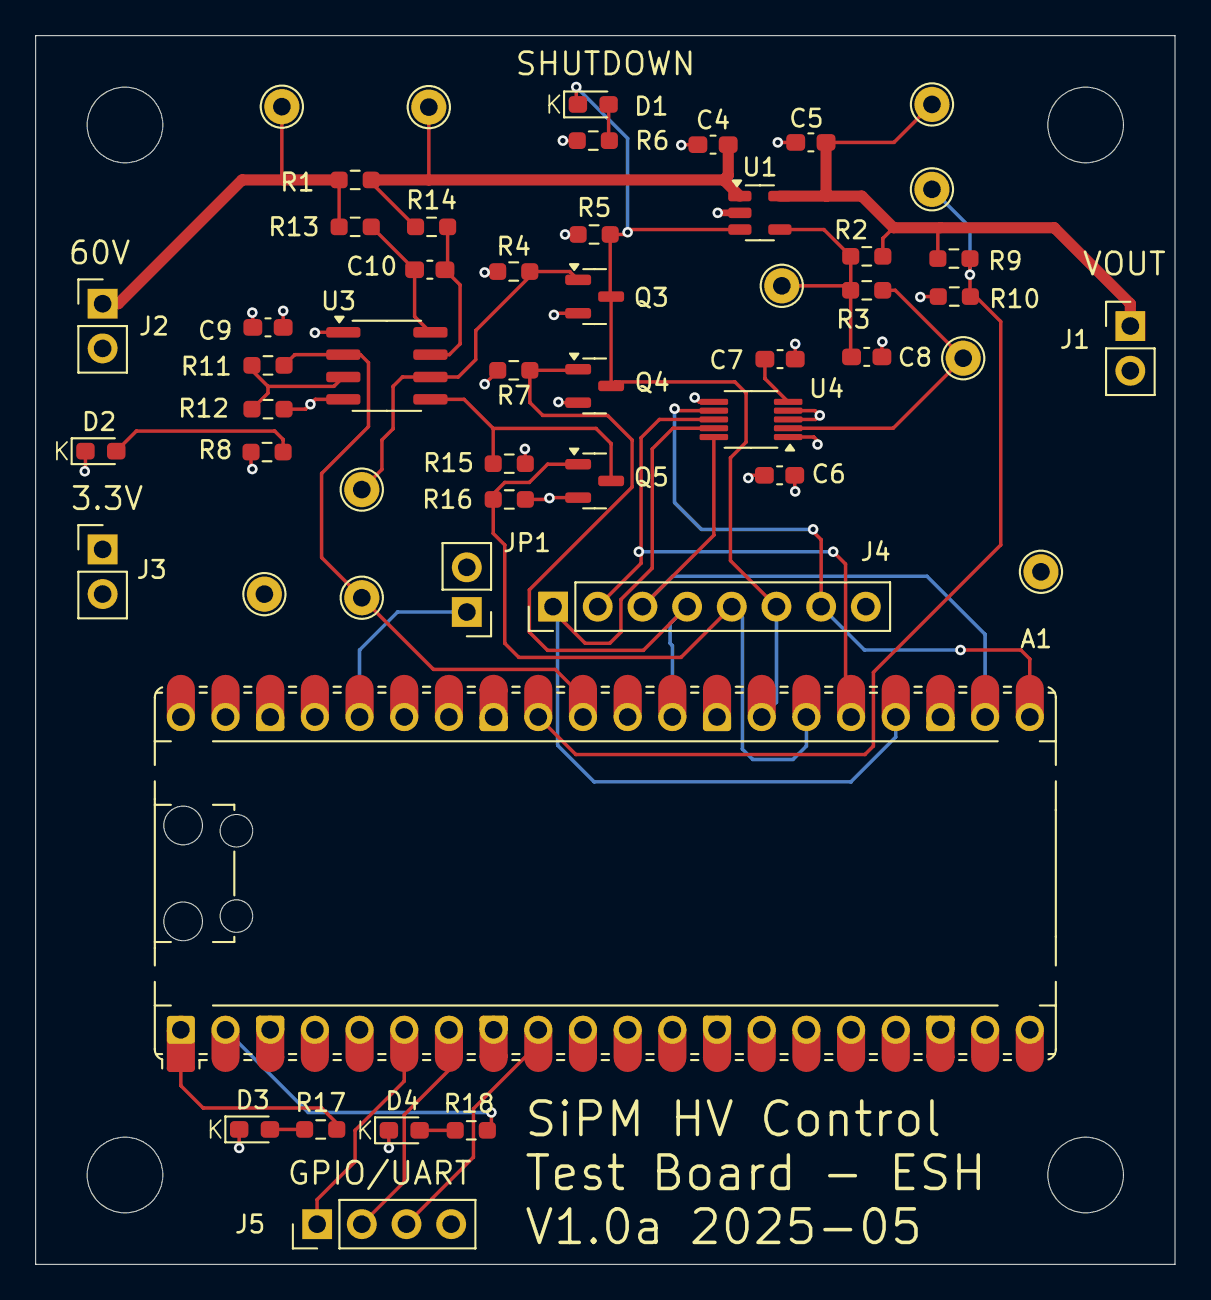
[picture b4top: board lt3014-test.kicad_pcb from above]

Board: 4 copper layers, 64.8 x 69.8 mm, 56 parts (0 on the bottom side), 32 nets.

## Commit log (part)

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2025-05-07 starting on bias voltage trim circuit
2025-05-08 working on sch
2025-05-08 working on layout
2025-05-09 new placement
2025-05-09 candidate V1.0 LT3014 board
2025-05-11 ordering
2025-05-12 small tweaks before V1.0 fab
2025-06-04 readme
2025-06-04 readme, schematic notes
2025-06-11 testing notes
2025-06-26 starting schem for HV/splitter for SiPM
2025-06-30 working on SiPM power supply schem
2025-06-30 starting placement
2025-06-30 random placement for area estimate
2025-06-30 add ISP
2025-06-30 fix some MCU pins
2025-07-01 working on 2.5 in placement
2025-07-01 routing madness
2025-07-02 working on bias filter changes
2025-07-02 routing
2025-07-03 routing almost done
2025-07-03 routing complete
2025-07-03 draft schematic PDF and Gerbers
2025-07-03 working on BOM
2025-07-03 finish BOM entries on schematic
2025-07-07 working on layout updates
2025-07-07 Candidate V1.0 for review/fab
2025-07-07 update PDF schematic
2025-07-08 Update gerber zip
2025-07-09 add mtg holes, L2 gnd fill
2025-07-10 finished V1.0 hv/splitter?
2025-07-23 testing
2025-07-23 testing digi pot
2025-07-29 digital pot working, updated ECOs
2025-08-04 software fixes, update README
2025-08-27 add temperature readout
2025-09-03 update software, add dark box
2025-09-10 dark box for testing
2025-09-10 tweak box
2025-09-11 docs and scripts
2025-09-12 new operating firmware, some doco
2026-02-03 update testing
2026-02-03 working on xtalk tests
2026-02-05 fix typo
2026-02-10 more testing
2026-02-26 More tests
2026-03-03 Update README and tweak voltage / ADC numbers
